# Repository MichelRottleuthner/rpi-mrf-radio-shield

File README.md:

# Adapter PCB to connect a [rpi802154-r1](http://openlabs.co/OSHW/Raspberry-Pi-802.15.4-radio) or [MRF24J40MA](http://www.microchip.com/wwwproducts/en/MRF24J40MA) module to nucleo / arduino boards

This simple shield can be used to connect the aforementioned radio modules to STM32 based boards like the [Nucleo-64 family](http://www.st.com/resource/en/user_manual/dm00105823.pdf) or various other boards that come with the well known arduino header.

The main reason for creating this shield is that I need a switch to disconnect the modules from their power supply in order to get rid of small leakage currents that occur even in sleep mode. This is done using a low side n-channel mosfet. Another point is that I need to do this for a few devices and I want them to have a more sturdy connection than the usual (error prone) breadboard and jumper wire tinkering. Think: plug&play instead of fiddling with loose wires and always looking up pin configurations again.

While tossing together a custom shield, why not add some little features that can be used for demo applications? For this there are two LEDs (D_PWR_1 and D_ACT1) connected to the radio's supply voltage and the CS pin to display if the device is powered and active. This allows to easily visualize duty-cycling applications.
Keeping in mind the initial purpose (low-power) the LEDs can be disconnected using the jumpers JP1 and JP2.

As a quick reference this is how the pins are connected:

| rpi802154-r1    | MRF24J40MA    | Nucleo Pin (name / connector) | Arduino Pin Name  |
|-----------------|---------------|-------------------------------|-------------------|
| +3.3V (2)       | Vin (10)      | +3V3 / CN6[4]                 | +3V3              |
| GND (6,10)      | GND (1,11,12) | *GND  / CN6[6,7], CN5[7]**    | GND               |
| MISO (4)        | SDO (7)       | PA6  / CN5[5]                 | D12               |
| MOSI (3)        | SDI (5)       | PA7  / CN5[4]                 | D11               |
| AT86_SEL (8)    | CS  (8)       | PB6  / CN5[3]                 | D10               |
| AT96_IRQ (12)   | INT (4)       | PA8  / CN9[8]                 | D7                |
| AT96_SLP_TR (9) | WAKE (3)      | PB10 / CN9[7]                 | D6                |
| AT96_RST (11)   | RESET (2)     | PB4  / CN9[6]                 | D5                |
| SCK (5)         | SCK (6)       | PA5  / CN5[6]                 | D13               |

\* The GND of the radios are actually connected to the drain pad of the FET which in turn has its source pad connected to GND of the board.

| Additional function      | Nucleo Pin (name / connector) | Arduino Pin Name  |
|--------------------------|-------------------------------|-------------------|
| FET drain (SOT-23 pad 1) | PA4  / CN8[3]                 | A2                |

---
## BOM

Below is the bill of materials for equipping the pcb. Obviously you can choose to use other parts as long as they have the same footprint and properties. For the lazy ones: you may want to look at [this pre-filled shopping cart at Mouser](https://www.mouser.com/ProjectManager/ProjectDetail.aspx?AccessID=bb2e666ecb) which contains all the parts needed to equip a single PCB.
The bare PCB can be ordered ad PCBs.io:
<a href="https://www.pcbs.io/share/8RMjO"></img></a>

| Component identifier      | Part                               | cnt. | Mouser Link                                                                      |
|---------------------------|------------------------------------|------|----------------------------------------------------------------------------------|
| J1, J2                    | 1x6 Pin Header 2.54mm pitch female | 2    | [855-M20-7820646](https://www.mouser.de/ProductDetail/855-M20-7820646)           |
| J3, J5                    | 1x8 Pin Header 2.54mm pitch male   | 2    | [538-22-28-0080](https://www.mouser.de/ProductDetail/538-22-28-0080)             |
| J4                        | 1x10 Pin Header 2.54mm pitch male  | 1    | [538-22-28-4102](https://www.mouser.de/ProductDetail/538-22-28-4102)             |
| J6                        | 1x6 Pin Header 2.54mm pitch male   | 1    | [538-22-28-4062](https://www.mouser.de/ProductDetail/538-22-28-4062)             |
| J7                        | 2x6 Pin Header 2.54mm pitch male   | 1    | [571-1037776](https://www.mouser.de/ProductDetail/571-1037776)                   |
| JP1, JP2                  | 1x2 Pin Header 2.54mm pitch male   | 2    | [571-826936-2](https://www.mouser.de/ProductDetail/571-826936-2)                 |
| -                         | Jumpers for JP1 and JP2            | 2    | [151-8010-E](https://www.mouser.de/ProductDetail/151-8010-E)                     |
| Q1                        | SOT-23 n-channel MOSFET            | 1    | [771-PMV20XNEAR](https://www.mouser.de/ProductDetail/771-PMV20XNEAR)             |
| R1, R2                    | 470R 0805 SMD resistor             | 2    | [652-CR0805FX-4700ELF ](https://www.mouser.de/ProductDetail/652-CR0805FX-1501ELF)|
| R3                        | 8.2k 0805 SMD resistor             | 1    | [652-CR0805JW-822ELF](https://www.mouser.de/ProductDetail/652-CR0805JW-822ELF)   |
| R4 or R5 (only 1 needed)  | 47k 0805 SMD resistor              | 1    | [71-CRCW0805-47K-E3](https://www.mouser.de/ProductDetail/71-CRCW0805-47K-E3)     |
| D_PWR_1                   | 0805 SMD LED (red)                 | 1    | [604-AP2012EC](https://www.mouser.de/ProductDetail/604-AP2012EC)                 |
| D_ACT_1                   | 0805 SMD LED (blue)                | 1    | [710-150080BS75000](https://www.mouser.de/ProductDetail/710-150080BS75000)       |

---
## Configuration

To define your prefered default state of the supply switch you can either fit a pull-up resistor to R5 or a pull-down to R4. While this is true for the FET listed in the BOM above, using another FET might reverse the logic and/or need other resistor values to work properly.

| Setting                   | Configuration             |
|---------------------------|---------------------------|
| Radio powered by default  | R4=not fitted / R5=47k    |
| Radio disabled by default | R4=47k / R5=not fitted    |
| LED D_PWR_1 disabled      | JP1=open                  |
| LED D_ACT1 disabled       | JP2=open                  |

---
### Using this shield with [RIOT](https://github.com/RIOT-OS/RIOT)
Depending on which module you want to use, copy one of the the following blocks to your applications Makefile.

**Note:**  Currently RIOT (more specifically it's radio driver(s)) doesn't handle power enable pins for the radios.
Using RIOT's auto-init feature together with "radio disabled by default" configuration will not work out of the box unless you add the needed power-on functionality to the beginning of the drivers init-function. As an alternative you can also just disable auto_init. This implies that you need to take care of enabling/disabling (and by that also initializing) the radio *manually*, wehen the R4/R5 pull resistors are configured to disable the supply by default.

**Note:**  On some boards the CS pin is shared with an LED and the [board_init](https://github.com/RIOT-OS/RIOT/blob/master/boards/common/nucleo/board.c) may overwrite the pin configuration. In this case you need to disable the initialization of the LED.

#### The following configs should work on all board with arduino pin-mappings
##### mrf24j40
```
USEMODULE += mrf24j40
CFLAGS += -DMRF24J40_PARAM_SPI=SPI_DEV\(0\)
CFLAGS += -DMRF24J40_PARAM_SPI_CLK=SPI_CLK_5MHZ
CFLAGS += -DMRF24J40_PARAM_CS=ARDUINO_PIN_10
CFLAGS += -DMRF24J40_PARAM_INT=ARDUINO_PIN_7
CFLAGS += -DMRF24J40_PARAM_RESET=ARDUINO_PIN_5

CFLAGS += -DRADIO_SUPPLY_SWITCH_PINT=ARDUINO_PIN_A2
```

##### at86rf2xx
```
USEMODULE += at86rf2xx
CFLAGS += -DAT86RF2XX_PARAM_SPI=SPI_DEV\(0\)
CFLAGS += -DAT86RF2XX_PARAM_SPI_CLK=SPI_CLK_5MHZ
CFLAGS += -DAT86RF2XX_PARAM_CS=ARDUINO_PIN_10
CFLAGS += -DAT86RF2XX_PARAM_INT=ARDUINO_PIN_7
CFLAGS += -DAT86RF2XX_PARAM_SLEEP=ARDUINO_PIN_6
CFLAGS += -DAT86RF2XX_PARAM_RESET=ARDUINO_PIN_5

CFLAGS += -DRADIO_SUPPLY_SWITCH_PINT=ARDUINO_PIN_A2
```

---

(c) by Michel Rottleuthner
The files in this repository are licensed under a Creative Commons Attribution 4.0 International License.
You should have received a copy of the license along with this work. If not, see .

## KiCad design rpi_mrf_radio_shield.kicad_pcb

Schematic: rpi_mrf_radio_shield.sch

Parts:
D_ACT1: LED; LED_0805_HandSoldering
D_PWR1: LED; LED_0805_HandSoldering
J1, J2: Conn_01x06_Female; Pin_Header_Straight_1x06_Pitch2.54mm
J3, J5: Conn_01x08_Male; Pin_Header_Straight_1x08_Pitch2.54mm
J4: Conn_01x10_Male; Pin_Header_Straight_1x10_Pitch2.54mm
J6: Conn_01x06_Male; Pin_Header_Straight_1x06_Pitch2.54mm
J7: Conn_02x06_Odd_Even; Pin_Header_Straight_2x06_Pitch2.54mm
JP1, JP2: Jumper; Pin_Header_Straight_1x02_Pitch2.54mm
LOGO1: Logo_Open_Hardware_Small; OSHW-Logo_5.7x6mm_SilkScreen
Q1: MMBF170; TSOT-23
R1, R2: 1.5k; R_0805_HandSoldering
R3: 8k; R_0805_HandSoldering
R4: 47k; R_0805_HandSoldering
R5: <inf>k; R_0805_HandSoldering

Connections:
CS: J2.2, J4.3, J7.10, JP1.2
FET_D: J1.1, J2.5, J2.6, J7.6, J7.11, JP2.2, Q1.3 (D)
GND: J3.6, J3.7, J4.7, Q1.2 (S), R4.1
INT: J1.4, J5.8, J7.2
MCU_SW: J6.3, R3.1
MISO: J2.1, J4.5, J7.7
MOSI: J1.5, J4.4, J7.5
unnamed: D_ACT1.1, R1.2
unnamed: D_PWR1.1, R2.2
unnamed: JP1.1, R1.1
unnamed: JP2.1, R2.1
unnamed: Q1.1 (G), R3.2, R4.2, R5.1
RST: J1.2, J5.6, J7.4
SCK: J1.6, J4.6, J7.9
VCC: D_ACT1.2, D_PWR1.2, J2.4, J3.4, J7.3, R5.2
WAKE: J1.3, J5.7, J7.8

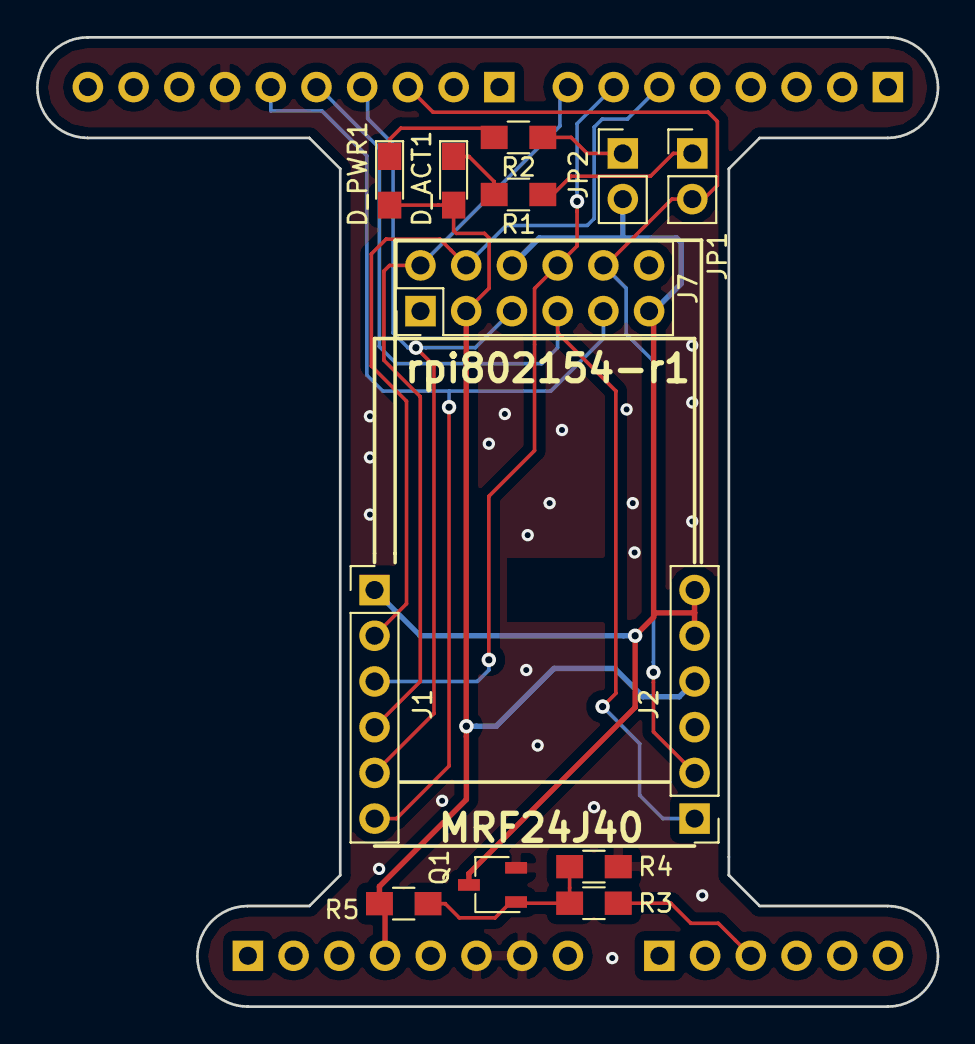
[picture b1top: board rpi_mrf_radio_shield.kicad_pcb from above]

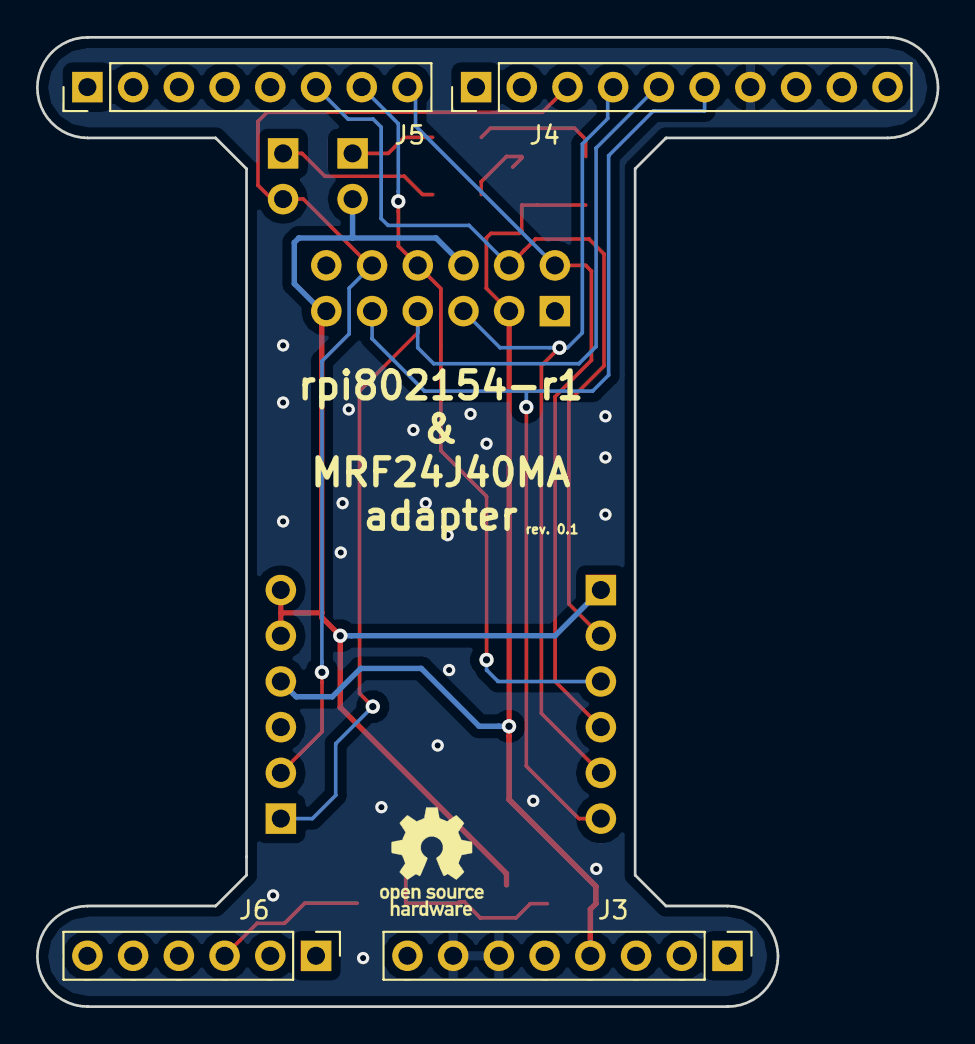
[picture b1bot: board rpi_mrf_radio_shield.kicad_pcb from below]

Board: 2 copper layers, 50.0 x 53.8 mm, 18 parts (5 on the bottom side), 16 nets.

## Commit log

2018-01-29 add LICENSE and README
2018-01-29 add KiCad files
2018-01-29 add gerbers
2018-01-29 add rendered images of top and bottom
2018-06-26 add connection details for nucleo144-446ze
2018-07-13 README: add connection details for at86rf2xx and adjust note wording
2018-07-13 README: fix wrong links and names in BOM
2018-07-13 README fix typo
2018-07-13 README: add note on shared CS/LED pin
2018-07-13 README: add order link
2018-07-13 README: fix order link
2018-07-23 README: change configuration to use arduino pin mappings of RIOT

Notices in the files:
README.md:
License: CC BY 4.0
